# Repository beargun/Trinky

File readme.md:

Trinky
=========

## A Trinket clone using only through-hole components

The goal of this project was to create a [Trinket](https://github.com/adafruit/Adafruit-Trinket-USB) clone using only through-hole components. 

### Goals

*   **Use only though-hole components**. Since there are no through-hole mini-USB B sockets, I opted for a USB A etched right on the board (similar to the [Digispark](http://digistump.com/products/1))
*   **Small footprint**. Get it at least as small as the original Trinket.
*   **Optional fuse**. I'm really fond of my USB ports, so for extra peace of mind I added a poly-fuse. I choose a surface-mount ptc fuse, as they tend to be faster than through hole versions. This fuse is optional (as it would break the first goal).  
*   **Different bootloader**. I slightly [altered the bootloader](https://github.com/beargun/Adafruit-Trinket-Gemma-Bootloader), to have it go into programming mode, only when the reset button is pressed. So when you power it up, your code will run immediately, instead of after 10 seconds.
*   **No voltage regulator**. The ATtiny85 will work on 2.7-5.5V. If you power your project using batteries, a voltage regulator will just decrease battery file. Just choose a battery with less than 5.5V. Also, I didn't have room for it. 

### Creating the board

Transfering the layout to the board using toner-transfer. You can see some paper residue on the toner. This doesn't hinder the etching
<br />

Etching the board in hydrochloric acid and hydrogen peroxide. I'm agitating the board using a modified cd-rom drive.
<br />

Almost done.
<br />

If you look closely you still see some copper. In hindsight I should have left it in the etching solution a bit longer.
<br />

With the toner removed you can clearly see the copper bridge. Easily fixed with a sharp knife.
<br />

All fixed. Note that I also cut away some of the outline. Otherwise I couldn't test for short using my multimeter
<br />

Holding it against the light reveals there are no more obvious shorts.
<br />

Holes drilled.
<br />

Outline cut using an electric scroll saw.
<br />

### Assembling the board

Since the led has to be at the top (the same side as the copper), I put the leads down, and then back up in the holes next to it. Otherwise you can't have the led flush with the board, as you have to be able to put the soldering iron underneath it.
<br />
<br />

Next add a jumper and the two zener diodes to the underside, and solder it.
<br />
<br />

The resistor for the led.
<br />

The two 68-Ohm resistors. **You should move the resistors more to the right, to make the button fit better.**
<br />

Note the solder bridge I accidentally made. I only noticed it when I was done, and did some final testing using my multimeter.
<br />

Remove two of the leads from the button. I also had to remove a bit of one corner. You shouldn't have to do that if you moved the resistor a bit more to the right.
<br />

Here I added the button and the 1800-Ohm resistor (Trinket uses 1500-Ohm). **You should put this resistor one the bottom. As it won't really fit, once you move the two resistors, as instructed above**
<br />

Here come the brains. I've already flashed my [altered bootloader](https://github.com/beargun/Adafruit-Trinket-Gemma-Bootloader) onto it.
<br />

Bend over the pins. 
<br />I also scraped away the trace between the two pads of the poly-fuse. If you don't add the poly-fuse you should just leave it there. 
<br />Here I've also tinned the USB connector. This will make it fit better into the USB socket, and prevent the copper from oxidizing and wearing out.
<br />

Here I soldered the pins, and added the optional poly-fuse. 
<br />

Because the ATtiny is at the bottom, I had to put shims under the header pins to raise them high enough to reach the board.
<br />

For a bit of extra bling, I added a few layers of nail varnish. This will prevent accidental short, oxidation and tin-whiskers (just kidding on the last one). I added some extra layers at the top right, where the board might touch the outside/shielding of the USB socket.
<br />

Too scale. The board ended up fractionally shorter (29.5mm) than the board of the real Trinket (note that mini-USB sticks out even more). It is however slightly wider. I could just cut away some more of the board, but I'd have to slightly move some components in the layout to match the width of the Trinket. Win some, lose some
<br />

<br />

<br />

And yes, it works!
<br />

Thank you for watching!

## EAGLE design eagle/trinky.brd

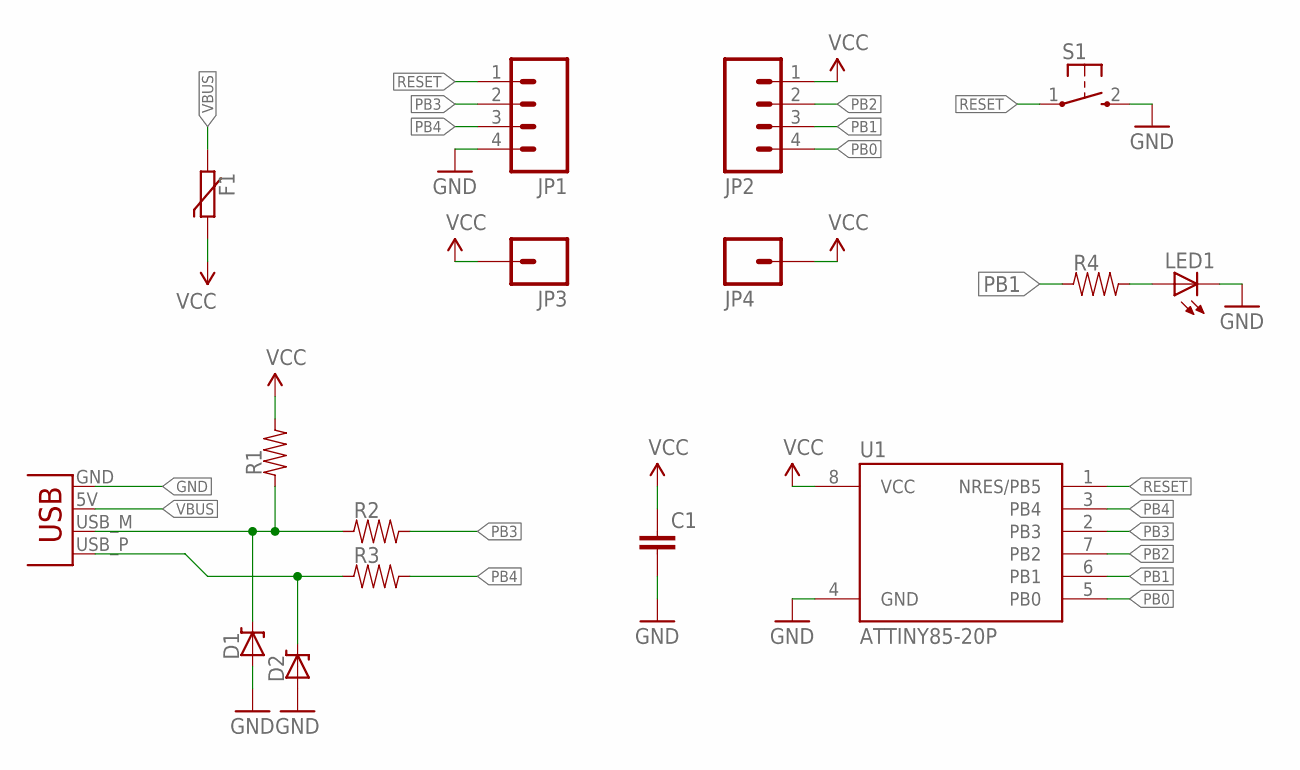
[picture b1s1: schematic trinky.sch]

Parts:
C1: CAPEZ; CAP-PTH-SMALLEZ
D1: ZENER-DIODE-AXIAL-0.385; SMALL-DIODE-0.385
D2: ZENER-DIODE-AXIAL-0.3; SMALL-DIODE-0.3
F1: 1812-RESETABLE-POLYFUSE; 1812-PTC-POLYFUSE
JP1, JP2: M04LONGPADS; 1X04_LONGPADS
JP3, JP4: M01PTH_LONGPAD; 1X01_LONGPAD
JP5: USBPCB; USB-A-PCB
LED1: LED3MM
R1: RESISTOR-AXIAL-0.2; AXIAL-0.2
R2, R3: RESISTOR-AXIAL-0.4; AXIAL-0.4
R4: RESISTOR-AXIAL-0.3; AXIAL-0.3
S1: TACTILE-SWITCH-2PINS-REMOVED; BUTTON-2PINS-REMOVED
U1: ATTINY85-20P; PDIP08_300MIL

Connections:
D+: D2.P$2, JP5.USB_P (D+), R3.P$1
D-: D1.P$2, JP5.USB_M (D-), R1.P$1, R2.P$1
GND: C1.2, D1.P$1, D2.P$1, JP1.4, JP5.GND, LED1.K (C), S1.2, U1.4 (GND)
unnamed: LED1.A, R4.P$2
PB0: JP2.4, U1.5 (PB0)
PB1: JP2.3, R4.P$1, U1.6 (PB1)
PB2: JP2.2, U1.7 (PB2)
PB3: JP1.2, R2.P$2, U1.2 (PB3)
PB4: JP1.3, R3.P$2, U1.3 (PB4)
RESET: JP1.1, S1.1, U1.1 (NRES/PB5)
VBUS: F1.P$1, JP5.5V (VBUS)
VCC: C1.1, F1.P$2, JP2.1, JP3.1, JP4.1, R1.P$2, U1.8 (VCC)

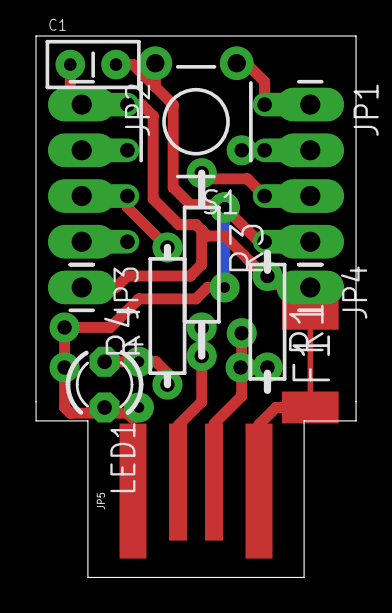
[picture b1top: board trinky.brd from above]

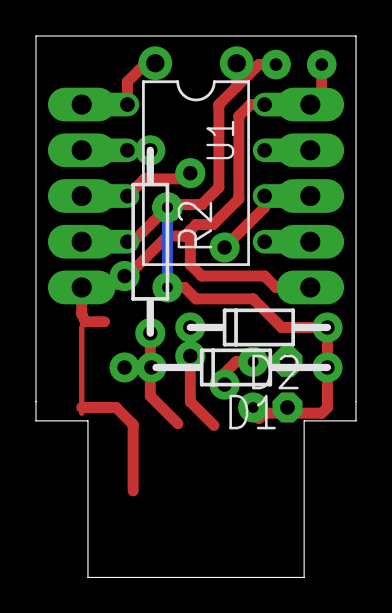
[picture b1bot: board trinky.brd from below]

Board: 2 copper layers, 17.8 x 30.1 mm, 16 parts (4 on the bottom side), 12 nets.

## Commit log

2014-02-15 readme
2014-02-16 more pictures
2014-02-16 update read me
2014-02-16 fixed hyperlink
2014-02-17 spell checked the readme file
2014-02-17 typo

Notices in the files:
parts and their libraries:
SparkFun-Connectors: Licensing: CC v3.0 Share-Alike You are welcome to use this library for commercial purposes.
